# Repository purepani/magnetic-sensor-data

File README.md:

# magnetic-sensor-data
data taken from the magnetic sensor

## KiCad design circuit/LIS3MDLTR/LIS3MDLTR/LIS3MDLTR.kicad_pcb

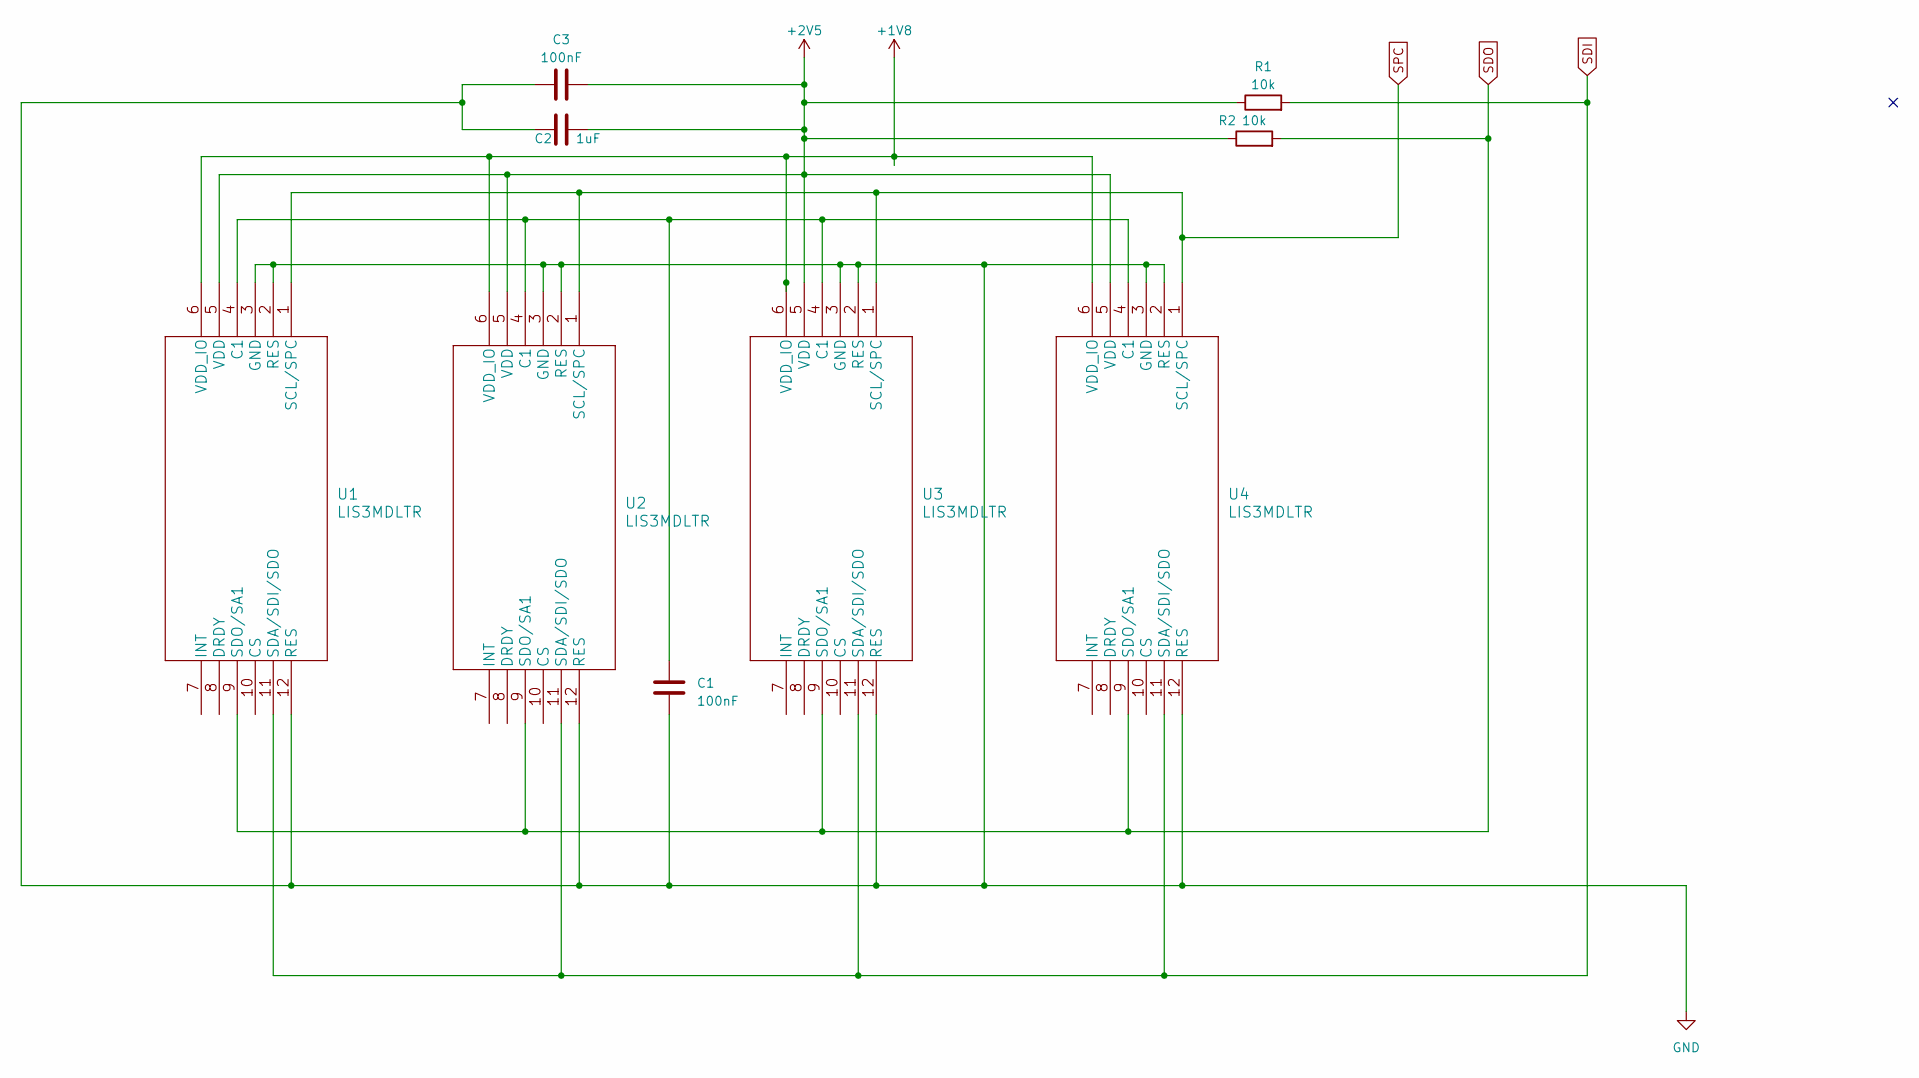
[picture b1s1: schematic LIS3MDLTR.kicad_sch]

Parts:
C1, C3: 100nF; C_0201_0603Metric
C2: 1uF; C_0201_0603Metric
R1, R2: 10k; R_0201_0603Metric
U1, U2, U3, U4: LIS3MDLTR

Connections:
+1V8: U1.6 (VDD_IO), U2.6 (VDD_IO), U3.6 (VDD_IO), U4.6 (VDD_IO)
+2V5: C2.2, C3.2, R1.1, R2.1, U1.5 (VDD), U2.5 (VDD), U3.5 (VDD), U4.5 (VDD)
GND: C1.2, C2.1, C3.1, U1.2 (RES), U1.3 (GND), U1.12 (RES), U2.2 (RES), U2.3 (GND), U2.12 (RES), U3.2 (RES), U3.3 (GND), U3.12 (RES), U4.2 (RES), U4.3 (GND), U4.12 (RES)
unnamed: C1.1, U1.4 (C1), U2.4 (C1), U3.4 (C1), U4.4 (C1)
SDI: R1.2, U1.11 (SDA/SDI/SDO), U2.11 (SDA/SDI/SDO), U3.11 (SDA/SDI/SDO), U4.11 (SDA/SDI/SDO)
SDO: R2.2, U1.9 (SDO/SA1), U2.9 (SDO/SA1), U3.9 (SDO/SA1), U4.9 (SDO/SA1)
SPC: U1.1 (SCL/SPC), U2.1 (SCL/SPC), U3.1 (SCL/SPC), U4.1 (SCL/SPC)

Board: 2 copper layers, 9 parts (0 on the bottom side), 7 nets, no tracks yet.

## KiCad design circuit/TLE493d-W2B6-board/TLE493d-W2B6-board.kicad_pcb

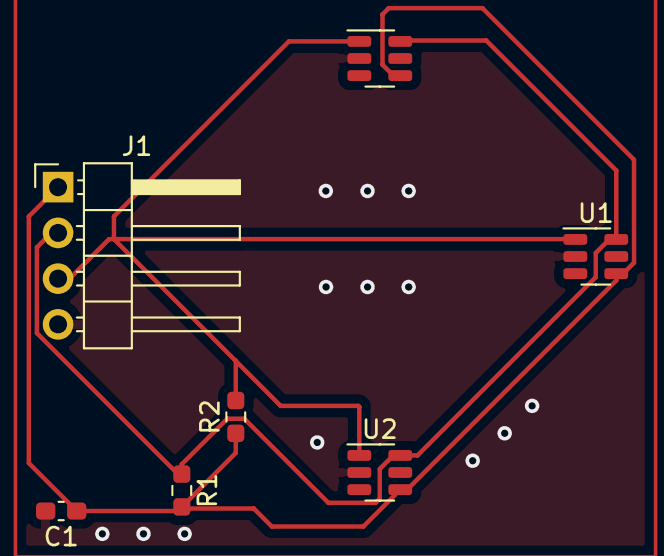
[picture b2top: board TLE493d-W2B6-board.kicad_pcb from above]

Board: 2 copper layers, 7 parts (0 on the bottom side), 4 nets.

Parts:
C1: 100nF; C_0603_1608Metric_Pad1.08x0.95mm_HandSolder
J1: Conn_01x04; PinHeader_1x04_P2.54mm_Horizontal
R1, R2: 1.2kOhm; R_0603_1608Metric_Pad0.98x0.95mm_HandSolder
U1, U2, U3: TLV493D; SOT-23-6

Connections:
+3V3: C1.1, J1.1, R1.2, R2.1, U1.4 (VDD), U2.4 (VDD), U3.4 (VDD)
GND: C1.2, J1.4, U1.2 (GND), U2.2 (GND), U3.2 (GND)
SCL: J1.3, R2.2, U1.1 (SCL/INT), U2.1 (SCL/INT), U3.1 (SCL/INT)
SDA: J1.2, R1.1, U1.6 (SDA/ADDR), U2.6 (SDA/ADDR), U3.6 (SDA/ADDR)

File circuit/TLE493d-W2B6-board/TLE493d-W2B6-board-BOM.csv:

"Id";"Designator";"Package";"Quantity";"Designation";"Supplier and ref";
1;"J1";"PinHeader_1x04_P2.54mm_Horizontal";1;"Conn_01x04";;;
2;"U3,U1,U2";"SOT-23-6";3;"TLV493D";;;
3;"R1,R2";"R_0603_1608Metric_Pad0.98x0.95mm_HandSolder";2;"1.2kOhm";;;
4;"C1";"C_0603_1608Metric_Pad1.08x0.95mm_HandSolder";1;"100nF";;;

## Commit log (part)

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2023-04-16 Added the 2.2 slice to the PIM04142023 test
2023-04-16 Added the 2.4000000000000004 slice to the PIM04142023 test
2023-04-16 Added the 2.8000000000000003 slice to the PIM04142023 test
2023-04-16 Added the 3.2 slice to the PIM04142023 test
2023-04-16 Added the 3.4000000000000004 slice to the PIM04142023 test
2023-04-16 Added the 3.8000000000000003 slice to the PIM04142023 test
2023-04-17 Added the 4.2 slice to the PIM04142023 test
2023-04-17 Added the 4.6000000000000005 slice to the PIM04142023 test
2023-04-17 Added the 4.800000000000001 slice to the PIM04142023 test
2023-04-17 Added the 5.2 slice to the PIM04142023 test
2023-04-17 Added the 5.6000000000000005 slice to the PIM04142023 test
2023-04-17 Added the 6.0 slice to the PIM04142023 test
2023-04-19 Modified sensor test for dipole
2023-05-11 Added the 0.0 slice to the PIM05112023_contest1 test
2023-05-11 Added the 2.0 slice to the PIM05112023_contest1 test
2023-05-11 Added the 4.0 slice to the PIM05112023_contest1 test
2023-05-11 Added the 5.0 slice to the PIM05112023_contest1 test
2023-05-11 Added the 1.0 slice to the PIM05112023_contest2 test
2023-05-11 Added the 3.0 slice to the PIM05112023_contest2 test
2023-05-11 Added the 5.0 slice to the PIM05112023_contest2 test
2023-05-17 Added the 0.0 slice to the PIM05172023_contest3 test
2023-05-17 Added the 2.0 slice to the PIM05172023_contest3 test
2023-05-17 Added the 4.0 slice to the PIM05172023_contest3 test
2023-05-17 Added the 5.0 slice to the PIM05172023_contest3 test
2023-05-24 Added the 0.0 slice to the PIM05242023_xcal2 test
2023-05-24 Added the 0.0 slice to the PIM05242023_xcal4 test
2023-05-24 Added the 0.0 slice to the PIM05242023_ycal2 test
2023-05-24 Added the 0.0 slice to the PIM05242023_ycal3 test
2023-05-24 Added the 0.0 slice to the PIM05242023_measurement test
2023-05-24 Added the 1.0 slice to the PIM05242023_measurement test
2023-05-24 Added the 2.0 slice to the PIM05242023_measurement test
2023-05-24 Added the 2.5 slice to the PIM05242023_measurement test
2023-05-24 Added the 3.5 slice to the PIM05242023_measurement test
2023-05-24 Added the 4.5 slice to the PIM05242023_measurement test
2023-06-07 Added the 0.0 slice to the PIM06072023_closemagnet test
2023-06-07 Added the 1.0 slice to the PIM06072023_closemagnet test
2023-06-07 Added the 3.0 slice to the PIM06072023_closemagnet test
2023-06-07 Added the 5.0 slice to the PIM06072023_closemagnet test
2023-06-07 Added the 1.0 slice to the PIM06072023_2cmAbove test
2023-06-07 Added the 2.0 slice to the PIM06072023_2cmAbove test
2023-06-07 Added the 4.0 slice to the PIM06072023_2cmAbove test
2023-06-07 Added the 0.0 slice to the PIM06072023_sen1con test
2023-06-07 Added the 1.0 slice to the PIM06072023_sen1con test
2023-06-07 Added the 1.5 slice to the PIM06072023_sen1con test
2023-06-07 Added the 2.5 slice to the PIM06072023_sen1con test
2023-06-07 Added the 3.5 slice to the PIM06072023_sen1con test
2023-06-07 Added the 4.0 slice to the PIM06072023_sen1con test
2023-06-07 Added the 5.0 slice to the PIM06072023_sen1con test
2023-06-09 Added the 0.5 slice to the PIM06092023_sen3rotateleft90 test
2023-06-09 Added the 1.5 slice to the PIM06092023_sen3rotateleft90 test
2023-06-09 Added the 2.0 slice to the PIM06092023_sen3rotateleft90 test
2023-06-09 Added the 3.0 slice to the PIM06092023_sen3rotateleft90 test
2023-06-09 Added the 4.0 slice to the PIM06092023_sen3rotateleft90 test
2023-06-09 Added the 5.0 slice to the PIM06092023_sen3rotateleft90 test
2023-06-14 Added the 0.0 slice to the PIM06142023_background test
2023-06-14 Added the 2.0 slice to the PIM06142023_background test
2023-06-14 Added the 4.0 slice to the PIM06142023_background test
2023-06-14 Added the 0.0 slice to the PIM06142023_magnet2 test
2023-06-14 Added the 0.5 slice to the PIM06142023_magnet2 test
2023-06-14 Added the 1.5 slice to the PIM06142023_magnet2 test
2023-06-14 Added the 2.5 slice to the PIM06142023_magnet2 test
2023-06-14 Added the 3.5 slice to the PIM06142023_magnet2 test
2023-06-14 Added the 4.0 slice to the PIM06142023_magnet2 test
2023-06-14 Added the 5.0 slice to the PIM06142023_magnet2 test
2023-06-14 Added the 0.5 slice to the PIM06142023_magnet3 test
2023-06-14 Added the 1.5 slice to the PIM06142023_magnet3 test
2023-06-14 Added the 2.0 slice to the PIM06142023_magnet3 test
2023-06-14 Added the 3.0 slice to the PIM06142023_magnet3 test
2023-06-14 Added the 4.0 slice to the PIM06142023_magnet3 test
2023-06-14 Added the 4.5 slice to the PIM06142023_magnet3 test
2023-06-15 Added the 0.0 slice to the PIM06152023_axistest test
2023-06-15 Added the 2.0 slice to the PIM06152023_axistest test
2023-06-15 Added the 0.0 slice to the PIM06152023_magnet4 test
2023-06-15 Added the 0.5 slice to the PIM06152023_magnet4 test
2023-06-15 Added the 1.5 slice to the PIM06152023_magnet4 test
2023-06-15 Added the 2.5 slice to the PIM06152023_magnet4 test
2023-06-15 Added the 3.5 slice to the PIM06152023_magnet4 test
2023-06-15 Added the 4.0 slice to the PIM06152023_magnet4 test
2023-06-15 Added the 5.0 slice to the PIM06152023_magnet4 test
2023-06-15 Added the 0.5 slice to the PIM06152023_magnet4retest test
2023-06-15 Added the 1.5 slice to the PIM06152023_magnet4retest test
2023-06-15 Added the 2.0 slice to the PIM06152023_magnet4retest test
2023-06-15 Added the 3.0 slice to the PIM06152023_magnet4retest test
2023-06-15 Added the 4.0 slice to the PIM06152023_magnet4retest test
2023-06-15 Added the 5.0 slice to the PIM06152023_magnet4retest test
2023-06-21 Added the 0.0 slice to the PIM06212023_magnet4contest test
2023-06-21 Added the 1.0 slice to the PIM06212023_magnet4contest test
2023-06-21 Added the 2.0 slice to the PIM06212023_magnet4contest test
2023-06-21 Added the 3.0 slice to the PIM06212023_magnet4contest test
2023-06-21 Added the 3.5 slice to the PIM06212023_magnet4contest test
2023-06-21 Added the 4.5 slice to the PIM06212023_magnet4contest test
2023-06-24 Add PIM06212023_magnet4contest/DataAvg.txt generated by calibrateprocessing.py
2023-06-25 changed caliibrate processing
2023-06-26 modified calibrations
2023-06-26 Added the 0.5 slice to the PIM06262023 test
2023-06-27 Added the 1.5 slice to the PIM06262023 test
2023-06-27 Added the 2.0 slice to the PIM06262023 test
2023-06-27 Added the 3.0 slice to the PIM06262023 test
2023-06-27 Added the 4.0 slice to the PIM06262023 test
2023-06-27 Added the 5.0 slice to the PIM06262023 test
2023-06-27 Add PIM06262023/DataAvg.txt generated by calibrateprocessing.py
2023-07-07 Added the 0.5 slice to the PIM07072023_4sensor test
2023-07-07 Added the 1.5 slice to the PIM07072023_4sensor test
2023-07-07 Added the 2.5 slice to the PIM07072023_4sensor test
2023-07-07 Added the 3.0 slice to the PIM07072023_4sensor test
2023-07-07 Added the 4.0 slice to the PIM07072023_4sensor test
2023-07-07 Added the 5.0 slice to the PIM07072023_4sensor test
2023-07-11 Added the 0.5 slice to the PIM07112023_4sensor test
2023-07-11 Added the 1.0 slice to the PIM07112023_4sensor test
2023-07-11 Added the 2.0 slice to the PIM07112023_4sensor test
2023-07-11 Added the 3.0 slice to the PIM07112023_4sensor test
2023-07-11 Added the 3.5 slice to the PIM07112023_4sensor test
2023-07-11 Added the 4.5 slice to the PIM07112023_4sensor test
2023-07-11 Added the 0.0 slice to the PIM07112023_4sensorCentered test
2023-07-11 Added the 1.0 slice to the PIM07112023_4sensorCentered test
2023-07-11 Added the 1.5 slice to the PIM07112023_4sensorCentered test
2023-07-11 Added the 2.5 slice to the PIM07112023_4sensorCentered test
2023-07-14 Added the 0.0 slice to the PIM07142023_cal2 test
2023-07-14 Added the 0.0 slice to the PIM07142023_cal4 test
2023-07-14 Added the 2.0 slice to the PIM07142023_cal4 test
2023-07-14 Added the 0.0 slice to the PIM07142023_4sensor test
2023-07-14 Added the 1.0 slice to the PIM07142023_4sensor test
2023-07-14 Added the 2.0 slice to the PIM07142023_4sensor test
2023-07-14 Added the 2.5 slice to the PIM07142023_4sensor test
2023-07-14 Added the 3.5 slice to the PIM07142023_4sensor test
2023-07-14 Added the 4.5 slice to the PIM07142023_4sensor test
2023-07-21 Added the data collected from the mannual setup
2023-07-24 Added manual data for 07242023
2023-07-24 Add manual lego measeurements
2023-07-25 changed calibration.py to use the prusa printer.
2023-07-25 Removed a space in a folder name
2023-07-25 Add measurement data and average measurements
2023-08-07 add comments for manual_data_collection about which sensor is which
2023-08-22 fixed address
2023-08-22 changed to mT
2023-08-22 modified the prusa calibration for the ciruit board
2023-09-20 Add data from MLX09192023
2023-09-20 Add data from MLX09192023_manual1
2023-09-22 Add data from MLX09212023_manual1
2023-09-22 Add data from MLX09222023_gamma2mm_xonly
2023-09-22 Add data from MLX09222023_gamma10mm_yonly
2023-11-20 Add data from MLX11202023_gamma1
2023-11-29 Add data from MLX11282023_manual1
2024-01-31 Add data from MLX01312024_gamma1
2024-01-31 Add data from MLX01312024_gamma3
2024-02-07 Add data from MLX02062024_D32N52_test2
2024-02-07 Add data from MLX02072024_D32N52_test1
2024-02-07 Add data from MLX02072024_D32N52_test3
2024-02-07 Add data from MLX02072024_D101N52_test1
2024-02-11 Add data from MLX02102024_D101N52_12mm
2024-02-11 Add data from MLX02102024_D101N52_z12mm
2024-02-12 Add data from MLX02120204_D201N52_z10mm
2024-02-12 Add data from MLX02122024_D201N52_z20mm
2024-02-12 Add data from MLX02122024_D21BN52_z15mm
2024-02-12 Add data from MLX02122024_D21BN52_z20mm
2024-02-12 Add data from MLX02122024_D301N52_z10mm
2024-02-13 Adds expected distance vs distance graphs
2024-02-13 Add data from MLX02122024_D301N52_z20mm
2024-02-13 Add data from MLX02132024_D31N52_z15mm
2024-02-13 Add data from MLX02132024_D32N52_z10mm
2024-02-13 Add data from MLX02132024_D32N52_z20mm
2024-02-13 Add data from MLX02132024_D32N52_z10mm1
2024-02-13 Add data from MLX02132024_D31N52_z15mm_s90
2024-02-14 Add data from MLX02142024_D32N52_z10mm_g4
2024-02-15 Add data from MLX02142024_D32N52_z20mm_g4
2024-02-15 Added the powerpoint with R^2 and error plots for different magnets
2024-02-28 Add data from MLX02282024_D32N52_z20mm_flipped
2024-03-06 Add data from MLX03062024_D32N52_gamma1
2024-03-20 Added the new gamma knife measurements
2024-04-01 Add data from MLX04012023_heat_off
2024-04-01 Add data from MLX04012024_temp_test2
2024-04-04 Add data from MLX04042024_test
2024-04-04 Add data from MLX04042024_dose_rate
2024-04-04 Add data from MLX04042024_dose_rate2
2024-04-11 Add data from MLX04112024_drift_test2
2024-04-27 added angle measurements again?
2024-05-01 Added the two analysis jupyter notebooks for the angle test
2024-05-08 Added new angle measurement data
2024-05-08 added gamma knife measurements
2024-05-11 Add the analysis for the latest angle testing and the 05/01/2024 gamma knife measurements
2024-06-05 added isocenter measurements
2024-06-06 added offset isocenter measurements
2024-06-12 Added analysis for the gamma knife measurements and the angle measurements with the fixed mounts
2024-06-19 added isocenter measurements with magnet surface at isocenter
2024-06-19 added analysis for latest isocenter measurements
2024-06-24 Added the analysis for the rotation about Z
2024-06-24 fixed name of folder
2024-06-25 added drift analysis
2024-06-25 updated drift analysis
2024-06-28 added overnight drift measurements
2024-07-02 90 degree drift test
2024-07-03 added about Z rotation measurements
2024-07-03 add more about Z rotation
2024-07-09 added another about Z rotation, radius about 5mm
2024-07-10 added more about z measurements
2024-07-10 added more r=10 about Z measurements
2024-07-10 r=10 about z
2024-07-17 added more rotational measurements
2024-07-17 more about Z measurements
2024-07-17 more about Z
2024-09-03 added gamma knife logs
2024-09-30 added gamma knife measurement logs
2024-10-17 added gamma knife measurements with rotation stage
2024-10-30 added more analysis for gamma knife measurements
2024-11-19 testing at z=30mm
2024-11-19 added z=40mm measurements
2024-12-18 added gk measurements
2024-12-20 added analysis
2025-01-22 added new magnet measurements
2025-01-22 added new magnet analysis
2025-01-22 more measuirements
2025-02-05 Added wire removal test
2025-04-02 multisensor analysis
2025-04-16 added multisensor data

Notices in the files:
parts and their libraries:
Copyright 2021 Accelerated Designs. All rights reserved.
